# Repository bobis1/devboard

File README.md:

# Eduboard
A devboard with an inbuilt screen and a software platform that should help beginners learn the basics of computer science. This is a rp2040 devboard at it's core.

I made this project because I wanted some experience working with devboards before I start something more complex. I also wanted to make something where a microcontroller was on a devboard already.

### Pictures

Above are renders made in blender.

### Assembly
The assembly of the devboard is relatively straight forward. The first thing you need to do is you need to get a hotplate and some soder paste to carefully soder on all the SMD components onto the pcb(This will be new to me as I have never done it before). Then you need to soder on the header pins onto the pcb by placing your sodering iron on the joint between the pcb and the pin and putting solder into that joint.

### Flashing
The flashing of this works the same way as a normal raspberry pi pico. You need to hold down SW_1 to start the flashing process.

### BOM
This BOM is for non PCBA. To be clear, I plan on using the bill of materials labeled [BOM](BOM.csv), [BOM-PCBA](BOM-PCBA.csv) is a BOM if you want to PCBA part of it.

|Reference                          |Qty|Value                      |Footprint                                                 |Datasheet                                                                        |Description                                                                                                        |Shopping Link                                                                                                                                                                                                                                                                                                                                                                                                                                                                                                                                         |Unit Price|Prices|Notes                                      |
|-----------------------------------|---|---------------------------|----------------------------------------------------------|---------------------------------------------------------------------------------|-------------------------------------------------------------------------------------------------------------------|------------------------------------------------------------------------------------------------------------------------------------------------------------------------------------------------------------------------------------------------------------------------------------------------------------------------------------------------------------------------------------------------------------------------------------------------------------------------------------------------------------------------------------------------------|----------|------|-------------------------------------------|
|C1,C2,C3,C4,C5,C6,C7,C8,C10,C11,C17|11 |0.1uf                      |C_0402_1005Metric_Pad0.74x0.62mm_HandSolder               |                                                                                 |Unpolarized capacitor                                                                                              |https://www.lcsc.com/product-detail/C1591.html?s_z=s_p_CL10B104KB8NNNC                                                                                                                                                                                                                                                                                                                                                                                                                                                                                |$0.00     |$0.46 |Minimum quantity: 50                       |
|C9,C12                             |2  |1uf                        |C_0603_1608Metric_Pad1.08x0.95mm_HandSolder               |                                                                                 |Unpolarized capacitor                                                                                              |https://www.lcsc.com/product-detail/C59782.html?s_z=n_q_CL10B105KO8NNNC                                                                                                                                                                                                                                                                                                                                                                                                                                                                               |$0.02     |$1.06 |Minimum quantity: 50                       |
|C13,C14, C19                       |3  |10uf                       |Capacitor_SMD:C_0603_1608Metric_Pad1.08x0.95mm_HandSolder |                                                                                 |Unpolarized capacitor                                                                                              |Samsung Electro-Mechanics CL10A106KP8NNNC                                                                                                                                                                                                                                                                                                                                                                                                                                                                                                             |$0.01     |$0.54 |Minimum quantity: 50                       |
|C15,C16                            |2  |33uf                       |C_0402_1005Metric_Pad0.74x0.62mm_HandSolder               |                                                                                 |Unpolarized capacitor                                                                                              |https://www.lcsc.com/product-detail/C76930.html?s_z=n_q_p_Capacitor_SMD%253AC_0201_0603Metric_Pad0.64x0.40mm&spm=wm.ssy.bg.0.xh&lcsc_vid=E1MNX1EDFlVaVF0CR1dYUVRWE1hcUFBQRgNcBF1QRwUxVlNeT1NdVlNeQ1VZVDsOAxUeFF5JWBYZEEoKFBINSQcJGk4dAgUUFAk%3D                                                                                                                                                                                                                                                                                                       |$0.01     |$0.54 |Minimum quantity: 50                       |
|C18,C20,C21                        |3  |10μf                       |C_0402_1005Metric_Pad0.74x0.62mm_HandSolder               |                                                                                 |Unpolarized capacitor                                                                                              |Samsung Electro-Mechanics CL10A106KP8NNNC                                                                                                                                                                                                                                                                                                                                                                                                                                                                                                             |$0.01     |$0.54 |Minimum quantity: 50                       |
|J1                                 |1  |USB_C_Receptacle_USB2.0_14P|Connector_USB:USB_C_Receptacle_HRO_TYPE-C-31-M-12         |https://www.usb.org/sites/default/files/documents/usb_type-c.zip                 |USB 2.0-only 14P Type-C Receptacle connector                                                                       |https://www.lcsc.com/product-detail/C165948.html?spm=wm.fly.bg.0.xh&lcsc_vid=E1MNX1EDFlVaVF0CR1dYUVRWE1hcUFBQRgNcBF1QRwUxVlNeT1NdVlRQT1BdXjsOAxUeFF5JWBILBhYFH08MFQUQEk8NCAlJJ                                                                                                                                                                                                                                                                                                                                                                        |$0.17     |$0.86 |                                           |
|J2,J3                              |2  |Conn_01x20                 |Connector_PinHeader_1.00mm:PinHeader_1x20_P1.00mm_Vertical|                                                                                 |Generic connector, single row, 01x20, script generated (kicad-library-utils/schlib/autogen/connector/)             |https://www.aliexpress.us/item/3256811704196969.html?spm=a2g0o.order_list.order_list_main.5.52e91802DwzU5C&gatewayAdapt=glo2usa                                                                                                                                                                                                                                                                                                                                                                                                                       |$2.36     |$2.36 |Minimum quantity: 5                        |
|J4                                 |1  |Conn_01x03                 |Connector_PinHeader_1.00mm:PinHeader_1x03_P1.00mm_Vertical|                                                                                 |Generic connector, single row, 01x03, script generated (kicad-library-utils/schlib/autogen/connector/)             |https://www.aliexpress.us/item/3256811704196969.html?spm=a2g0o.order_list.order_list_main.5.52e91802DwzU5C&gatewayAdapt=glo2usa                                                                                                                                                                                                                                                                                                                                                                                                                       |$0.00     |$0.00 |                                           |
|L1                                 |1  |2.2μH                      |Inductor_SMD:L_6.3x6.3_H3                                 |                                                                                 |Inductor                                                                                                           |https://www.lcsc.com/product-detail/C52722262.html?s_z=h_q_inductor%25202.2uh&spm=wm.fly.bg.0.xh&lcsc_vid=E1MNX1EDFlVaVF0CR1dYUVRWE1hcUFBQRgNcBF1QRwUxVlNeT1NdV1xeRlFYVjsOAxUeFF5JWBYZEEoKFBINSQcJGk4eFQsCAgIaSgADAwAHC0slQ1lZX1dVR1NADxALGw%3D%3D                                                                                                                                                                                                                                                                                                    |$0.04     |$0.41 |This comes with the above 01x20 pin headers|
|R1                                 |1  |5.1KΩ                      |Resistor_SMD:R_0402_1005Metric_Pad0.72x0.64mm             |                                                                                 |Resistor                                                                                                           |https://www.mouser.com/en/ProductDetail/Vishay/CRCW04025K10FKED?qs=s0g2FHNyNFj8r6Uw5EJZ%2Fw%3D%3D                                                                                                                                                                                                                                                                                                                                                                                                                                                     |$0.10     |$0.10 |Minimum quanity: 10                        |
|R2                                 |1  |5.1KΩ                      |Resistor_SMD:R_0402_1005Metric_Pad0.72x0.64mm             |                                                                                 |Resistor                                                                                                           |https://www.mouser.com/en/ProductDetail/Vishay/CRCW04025K10FKED?qs=s0g2FHNyNFj8r6Uw5EJZ%2Fw%3D%3D                                                                                                                                                                                                                                                                                                                                                                                                                                                     |$0.10     |$0.10 |                                           |
|R3,R4                              |2  |27Ω                        |Resistor_SMD:R_0402_1005Metric_Pad0.72x0.64mm             |                                                                                 |Resistor                                                                                                           |https://www.mouser.com/en/ProductDetail/YAGEO/RC0402FR-0727RL?qs=UOUeRUa%252B8Wlb37UyFHw9Bw%3D%3D                                                                                                                                                                                                                                                                                                                                                                                                                                                     |$0.10     |$0.20 |                                           |
|R5,R6                              |2  |1KΩ                        |Resistor_SMD:R_0402_1005Metric_Pad0.72x0.64mm             |                                                                                 |Resistor                                                                                                           |https://www.mouser.com/en/ProductDetail/YAGEO/RC0402FR-071KL?qs=V1yeUXFNrknDEmWLmm5v6g%3D%3D                                                                                                                                                                                                                                                                                                                                                                                                                                                          |$0.10     |$0.20 |                                           |
|R7                                 |1  |10KΩ                       |Resistor_SMD:R_0402_1005Metric_Pad0.72x0.64mm             |                                                                                 |Resistor                                                                                                           |https://www.mouser.com/en/ProductDetail/YAGEO/RC0402FR-0710KL?qs=I1mnnYJTTsxUoNwrUsQExA%3D%3D                                                                                                                                                                                                                                                                                                                                                                                                                                                         |$0.10     |$0.10 |                                           |
|R8                                 |1  |100Ω                       |Resistor_SMD:R_0402_1005Metric_Pad0.72x0.64mm             |                                                                                 |Resistor                                                                                                           |https://www.mouser.com/en/ProductDetail/Vishay/CRCW0402100RFKED?qs=OlqPY1CiralT1EG%2F62gJpQ%3D%3D                                                                                                                                                                                                                                                                                                                                                                                                                                                     |$0.10     |$0.10 |                                           |
|SW1,SW2                            |2  |SW_Push                    |Button_Switch_SMD:SW_SPST_TS-1088-xR020                   |                                                                                 |Push button switch, generic, two pins                                                                              |https://www.lcsc.com/product-detail/C49234124.html?s_z=n_q_t_tactile%2520switches%2520smd&spm=wm.fly.bg.1.xh___wm.ssy.tc.0.tz&lcsc_vid=E1MNX1EDFlVaVF0CR1dYUVRWE1hcUFBQRgNcBF1QRwUxVlNeT1BdV1RQQlVaXzsOAxUeFF5JWBYZEEoKFBINSQcJGk4dAgUUFAk%3D                                                                                                                                                                                                                                                                                                         |$0.02     |$0.49 |                                           |
|U1                                 |1  |RP2040                     |Package_DFN_QFN:QFN-56-1EP_7x7mm_P0.4mm_EP3.2x3.2mm       |https://datasheets.raspberrypi.com/rp2040/rp2040-datasheet.pdf                   |A microcontroller by Raspberry Pi, Dual ARM Cortex-M0+, 133MHz, no flash, 264KB SRAM, 8 PIO state machines, VQFN-56|https://www.digikey.com/en/products/detail/raspberry-pi/SC0908-7/14306009?src=raspberrypi                                                                                                                                                                                                                                                                                                                                                                                                                                                             |$0.92     |$0.92 |                                           |
|U2                                 |1  |MCP1700x-120xxMB           |Package_TO_SOT_SMD:SOT-89-3                               |http://ww1.microchip.com/downloads/en/DeviceDoc/20001826D.pdf                    |250mA Low Quiscent Current LDO, 1.2V output, SOT-89                                                                |https://www.microchip.com/en-us/product/mcp1700#Purchase(3 leads, SOT-89 packaging)                                                                                                                                                                                                                                                                                                                                                                                                                                                                   |$0.51     |$0.51 |                                           |
|U3                                 |1  |W25Q128JVS                 |Package_SO:SOIC-8_5.3x5.3mm_P1.27mm                       |https://www.winbond.com/resource-files/w25q128jv_dtr%20revc%2003272018%20plus.pdf|128Mbit / 16MiB Serial Flash Memory, Standard/Dual/Quad SPI, 2.7-3.6V, SOIC-8                                      |https://www.lcsc.com/product-detail/C97521.html?s_z=n_q_p_128M-BIT%2520SERIAL%2520FLASH%2520MEMORY%2520WITH%2520DUAL%252FQUAD%2520SPI&spm=wm.ssy.bg.23.xh&lcsc_vid=E1MNX1EDFlVaVF0CR1dYUVRWE1hcUFBQRgNcBF1QRwUxVlNeT1BcXlFfTlBWVTsOAxUeFF5JWBYZEEoKFBINSQcJGk4dAgUUFAk%3D OR https://www.lcsc.com/product-detail/C97521.html?s_z=n_q_p_128M-BIT%2520SERIAL%2520FLASH%2520MEMORY%2520WITH%2520DUAL%252FQUAD%2520SPI&spm=wm.ssy.bg.22.xh&lcsc_vid=E1MNX1EDFlVaVF0CR1dYUVRWE1hcUFBQRgNcBF1QRwUxVlNeT1BcXlFfTlBWVTsOAxUeFF5JWBYZEEoKFBINSQcJGk4dAgUUFAk%3D|$2.62     |$2.62 |                                           |
|U4                                 |1  |ER_OLEDM0.91_1x-I2C        |Display:ER_OLEDM0.91_1x-I2C                               |https://www.buydisplay.com/download/manual/ER-OLEDM0.91-1_Datasheet.pdf          |SSD1306 OLED module, 0.91 inch, 128x32, I2C                                                                        |https://www.buydisplay.com/i2c-white-0-91-inch-oled-display-module-128x32-arduino-raspberry-pi                                                                                                                                                                                                                                                                                                                                                                                                                                                        |$2.80     |$2.80 |                                           |
|U5                                 |1  |TPS63000                   |Package_SON:Texas_DRC0010J_ThermalVias                    |http://www.ti.com/lit/ds/symlink/tps63000.pdf                                    |Buck-Boost Converter, 1.8-5.5V Input Voltage, 1.8A Switch Current, Adjustable 1.2-5.5V Output Voltage, VSON-10     |https://www.ti.com/product/TPS63000/part-details/TPS63000DRCR                                                                                                                                                                                                                                                                                                                                                                                                                                                                                         |$2.00     |$2.00 |                                           |
|XT1                                |1  |                           |JST-PH-2.:JST-PH-2                                        |                                                                                 |                                                                                                                   |https://www.adafruit.com/product/1769                                                                                                                                                                                                                                                                                                                                                                                                                                                                                                                 |$0.75     |$0.75 |                                           |
|Y2                                 |1  |Crystal_GND24              |Crystal:Crystal_SMD_3225-4Pin_3.2x2.5mm                   |                                                                                 |Four pin crystal, GND on pins 2 and 4                                                                              |https://www.lcsc.com/product-detail/C13738.html?s_z=n_q_p_crystal%25203225-4Pin_3.2x2.5mm&spm=wm.ssy.bg.0.xh&lcsc_vid=E1MNX1EDFlVaVF0CR1dYUVRWE1hcUFBQRgNcBF1QRwUxVlNeT1BcX1JRQFhYUDsOAxUeFF5JWBYZEEoKFBINSQcJGk4%3D                                                                                                                                                                                                                                                                                                                                  |$0.09     |$0.47 |                                           |
|                                   |   |                           |                                                          |                                                                                 |                                                                                                                   |                                                                                                                                                                                                                                                                                                                                                                                                                                                                                                                                                      |          |      |Minimum quanity: 5                         |
|                                   |   |                           |                                                          |                                                                                 |                                                                                                                   |                                                                                                                                                                                                                                                                                                                                                                                                                                                                                                                                                      |          |      |                                           |
|                                   |   |                           |                                                          |                                                                                 |                                                                                                                   |                                                                                                                                                                                                                                                                                                                                                                                                                                                                                                                                                      |          |      |                                           |
|                                   |   |                           |Subtotal:                                                 |$0.00                                                                            |                                                                                                                   |                                                                                                                                                                                                                                                                                                                                                                                                                                                                                                                                                      |          |      |                                           |
|                                   |   |                           |PCB Fee:                                                  |$0.00                                                                            |                                                                                                                   |                                                                                                                                                                                                                                                                                                                                                                                                                                                                                                                                                      |          |      |                                           |
|                                   |   |                           |Shipping:                                                 |$2.00                                                                            |                                                                                                                   |                                                                                                                                                                                                                                                                                                                                                                                                                                                                                                                                                      |          |      |                                           |
|                                   |   |                           |Tariff:                                                   |$0.00                                                                            |                                                                                                                   |                                                                                                                                                                                                                                                                                                                                                                                                                                                                                                                                                      |          |      |                                           |
|                                   |   |                           |PCBA fee:                                                 |$45.96                                                                           |                                                                                                                   |                                                                                                                                                                                                                                                                                                                                                                                                                                                                                                                                                      |          |      |                                           |
|                                   |   |                           |Total Price                                               |$47.96                                                                           |                                                                                                                   |                                                                                                                                                                                                                                                                                                                                                                                                                                                                                                                                                      |          |      |                                           |

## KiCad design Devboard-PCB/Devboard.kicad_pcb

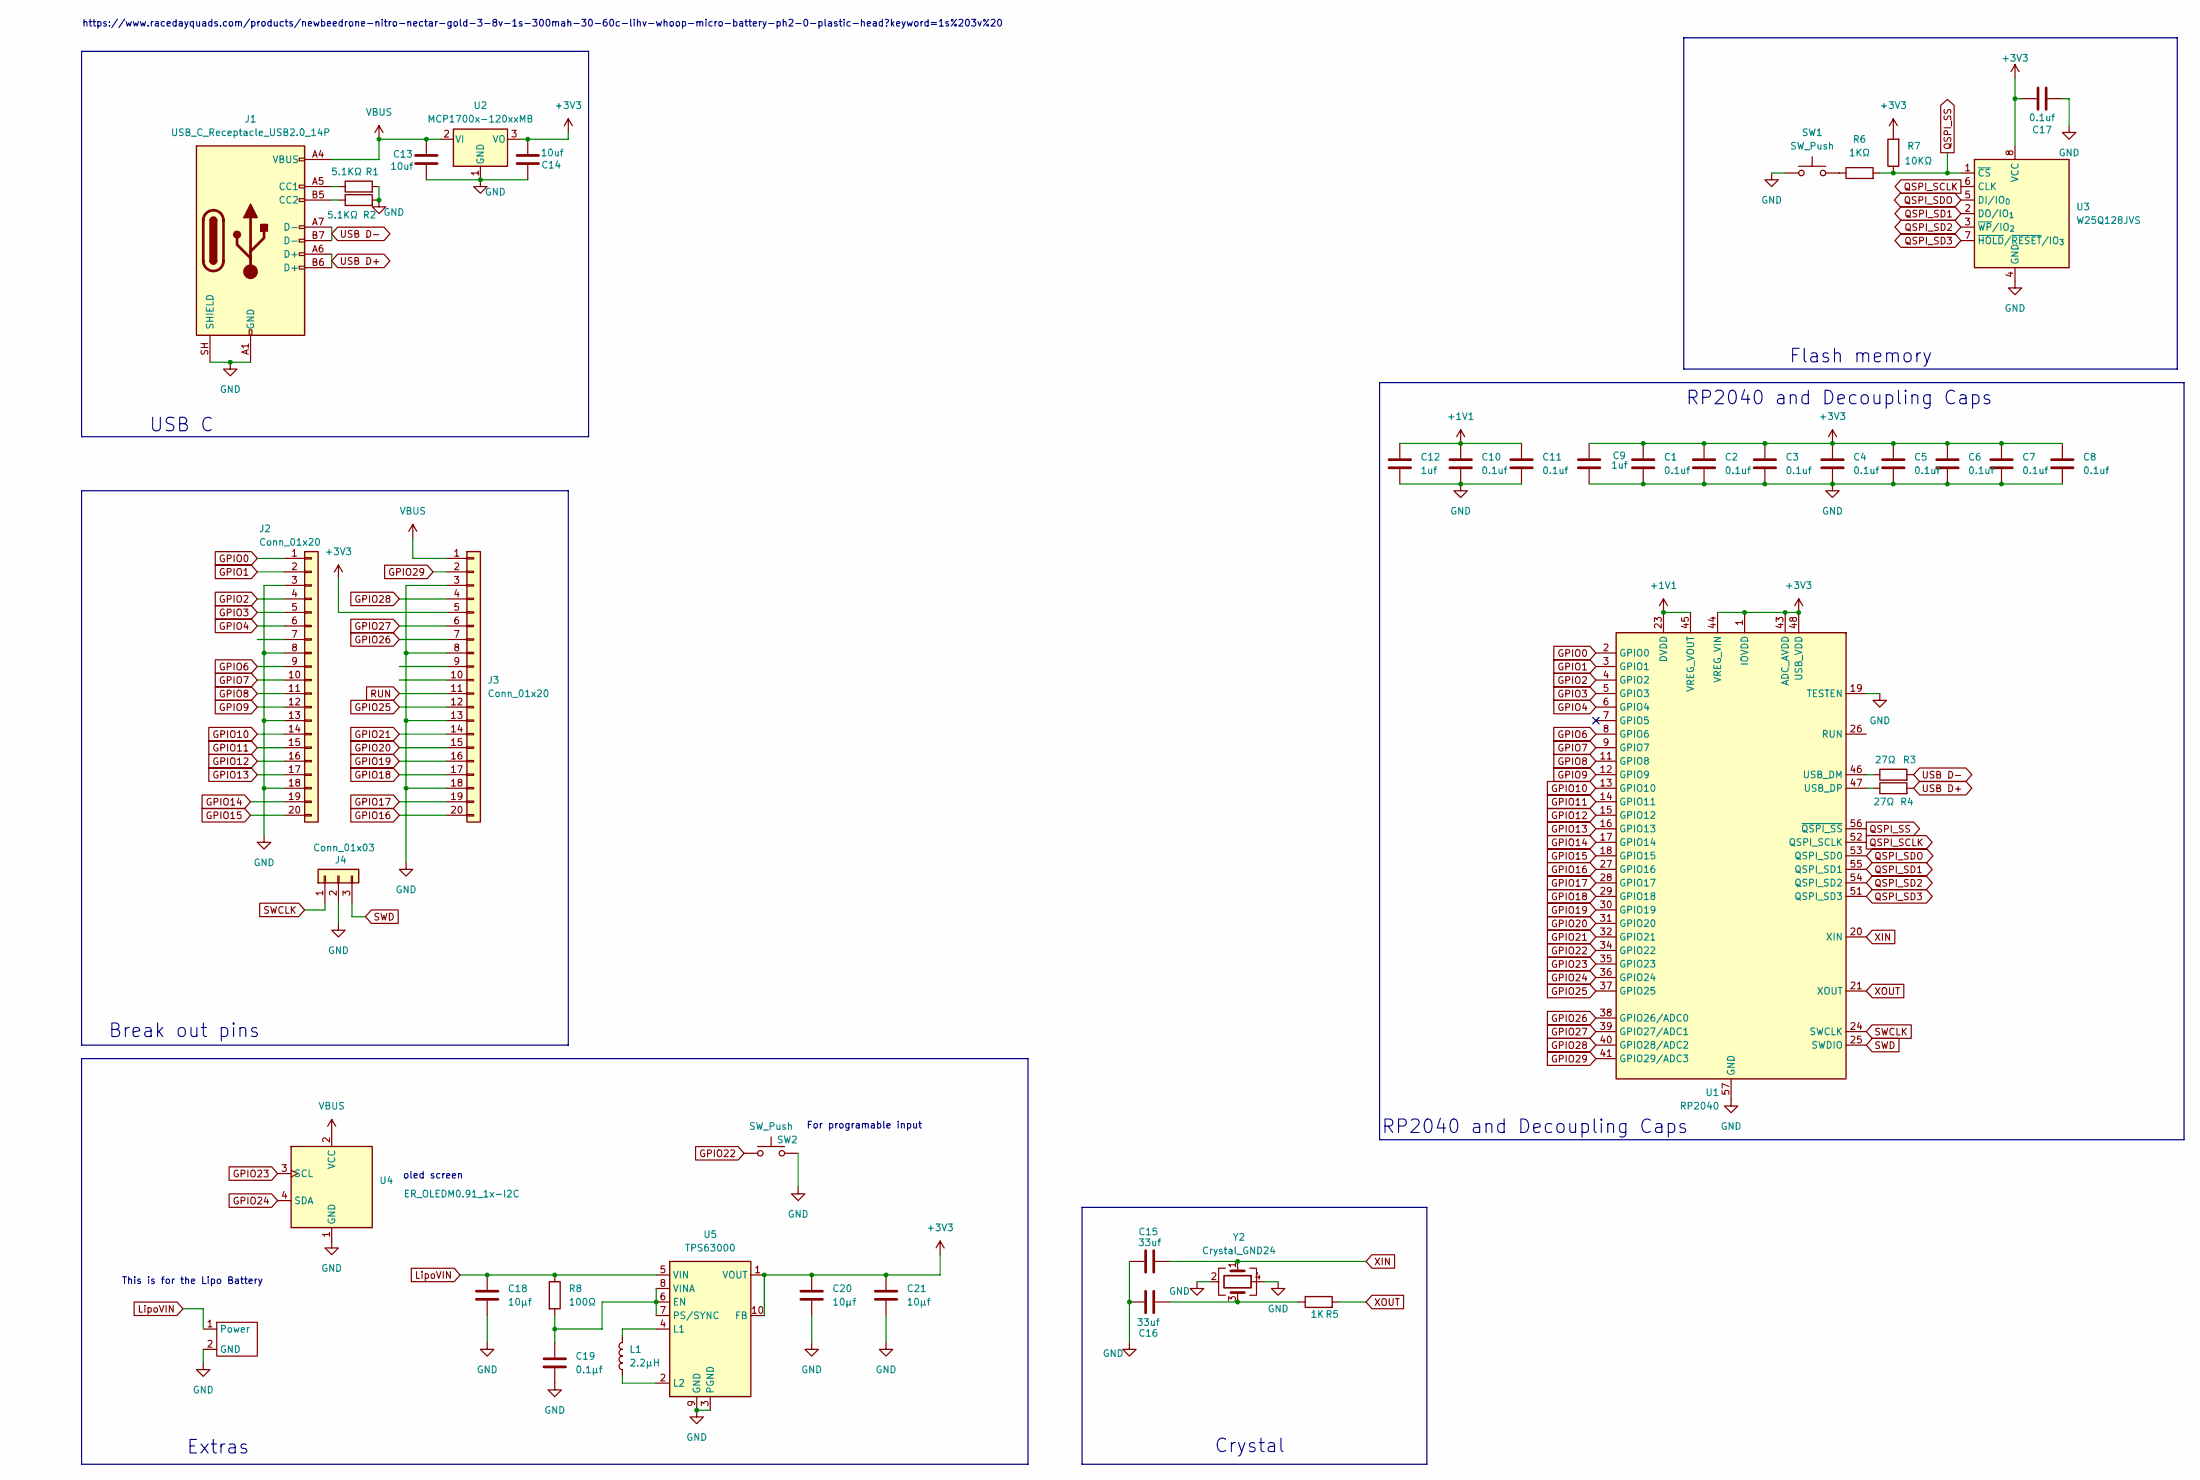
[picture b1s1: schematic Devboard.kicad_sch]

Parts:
C1, C2, C3, C4, C5, C6, C7, C8, C10, C11, C17: 0.1uf; C_0402_1005Metric_Pad0.74x0.62mm_HandSolder
C9: 1uf; C_0603_1608Metric_Pad1.08x0.95mm_HandSolder
C12: 1uf; C_0402_1005Metric_Pad0.74x0.62mm_HandSolder
C13, C14: 10uf; C_0402_1005Metric_Pad0.74x0.62mm_HandSolder
C15, C16: 33uf; C_0402_1005Metric_Pad0.74x0.62mm_HandSolder
C18, C20, C21: 10μf; C_0603_1608Metric_Pad1.08x0.95mm_HandSolder
C19: 0.1μf; C_0402_1005Metric_Pad0.74x0.62mm_HandSolder
J1: USB_C_Receptacle_USB2.0_14P; USB_C_Receptacle_HRO_TYPE-C-31-M-12
J2, J3: Conn_01x20; PinHeader_1x20_P1.00mm_Vertical
J4: Conn_01x03; PinHeader_1x03_P1.00mm_Vertical
L1: 2.2μH; L_6.3x6.3_H3
R1, R2: 5.1KΩ; R_0402_1005Metric
R3, R4: 27Ω; R_0402_1005Metric
R5: 1K; R_0402_1005Metric
R6: 1KΩ; R_0402_1005Metric
R7: 10KΩ; R_0402_1005Metric
R8: 100Ω; R_0201_0603Metric
SW1, SW2: SW_Push; SW_SPST_TS-1088-xR020
U1: RP2040; QFN-56-1EP_7x7mm_P0.4mm_EP3.2x3.2mm
U2: MCP1700x-120xxMB; SOT-89-3
U3: W25Q128JVS; SOIC-8_5.3x5.3mm_P1.27mm
U4: ER_OLEDM0.91_1x-I2C
U5: TPS63000; Texas_DRC0010J_ThermalVias
XT1: JST-PH-2
Y2: Crystal_GND24; Crystal_SMD_3225-4Pin_3.2x2.5mm

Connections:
+1V1: C10.1, C11.1, C12.1, U1.23 (DVDD), U1.45 (VREG_VOUT), U1.50 (DVDD)
+3V3: C1.1, C2.1, C3.1, C4.1, C5.1, C6.1, C7.1, C8.1, C9.1, C14.2, C17.1, C20.1, C21.1, J3.5, R7.2, U1.1 (IOVDD), U1.10 (IOVDD), U1.22 (IOVDD), U1.33 (IOVDD), U1.42 (IOVDD), U1.43 (ADC_AVDD), U1.44 (VREG_VIN), U1.48 (USB_VDD), U1.49 (IOVDD), U2.3 (VO), U3.8 (VCC), U5.1 (VOUT), U5.10 (FB)
GND: C1.2, C2.2, C3.2, C4.2, C5.2, C6.2, C7.2, C8.2, C9.2, C10.2, C11.2, C12.2, C13.2, C14.1, C15.1, C16.1, C17.2, C18.2, C19.2, C20.2, C21.2, J1.A1 (GND), J1.A12 (GND), J1.B1 (GND), J1.B12 (GND), J1.SH (SHIELD), J2.3, J2.8, J2.13, J2.18, J3.3, J3.8, J3.13, J3.18, J4.2, R1.2, R2.2, SW1.1, SW2.2, U1.19 (TESTEN), U1.57 (GND), U2.1 (GND), U3.4 (GND), U4.1 (GND), U5.3 (PGND), U5.9 (GND), U5.11 (PGND), XT1.2 (GND), Y2.2 (G), Y2.4 (G)
GPIO0: J2.1, U1.2 (GPIO0)
GPIO1: J2.2, U1.3 (GPIO1)
GPIO2: J2.4, U1.4 (GPIO2)
GPIO3: J2.5, U1.5 (GPIO3)
GPIO4: J2.6, U1.6 (GPIO4)
GPIO6: J2.9, U1.8 (GPIO6)
GPIO7: J2.10, U1.9 (GPIO7)
GPIO8: J2.11, U1.11 (GPIO8)
GPIO9: J2.12, U1.12 (GPIO9)
GPIO10: J2.14, U1.13 (GPIO10)
GPIO11: J2.15, U1.14 (GPIO11)
GPIO12: J2.16, U1.15 (GPIO12)
GPIO13: J2.17, U1.16 (GPIO13)
GPIO14: J2.19, U1.17 (GPIO14)
GPIO15: J2.20, U1.18 (GPIO15)
GPIO16: J3.20, U1.27 (GPIO16)
GPIO17: J3.19, U1.28 (GPIO17)
GPIO18: J3.17, U1.29 (GPIO18)
GPIO19: J3.16, U1.30 (GPIO19)
GPIO20: J3.15, U1.31 (GPIO20)
GPIO21: J3.14, U1.32 (GPIO21)
GPIO22: SW2.1, U1.34 (GPIO22)
GPIO23: U1.35 (GPIO23), U4.3 (SCL)
GPIO24: U1.36 (GPIO24), U4.4 (SDA)
GPIO25: J3.12, U1.37 (GPIO25)
GPIO26: J3.7, U1.38 (GPIO26/ADC0)
GPIO27: J3.6, U1.39 (GPIO27/ADC1)
GPIO28: J3.4, U1.40 (GPIO28/ADC2)
GPIO29: J3.2, U1.41 (GPIO29/ADC3)
LipoVIN: C18.1, R8.1, U5.5 (VIN), XT1.1 (Power)
unnamed: C16.2, R5.1, Y2.3
unnamed: J1.A5 (CC1), R1.1
unnamed: J1.B5 (CC2), R2.1
unnamed: R6.1, SW1.2
unnamed: R3.1, U1.46 (USB_DM)
unnamed: R4.1, U1.47 (USB_DP)
unnamed: C19.1, R8.2, U5.6 (EN), U5.7 (PS/SYNC), U5.8 (VINA)
unnamed: L1.2, U5.4 (L1)
unnamed: L1.1, U5.2 (L2)
QSPI_SCLK: U1.52 (QSPI_SCLK), U3.6 (CLK)
QSPI_SD1: U1.55 (QSPI_SD1), U3.2 (DO/IO_{1})
QSPI_SD2: U1.54 (QSPI_SD2), U3.3 (~WP/IO_{2})
QSPI_SD3: U1.51 (QSPI_SD3), U3.7 (~HOLD/~RESET/IO_{3})
QSPI_SDO: U1.53 (QSPI_SD0), U3.5 (DI/IO_{0})
QSPI_SS: R6.2, R7.1, U1.56 (~QSPI_SS), U3.1 (~CS)
RUN: J3.11
SWCLK: J4.1, U1.24 (SWCLK)
SWD: J4.3, U1.25 (SWDIO)
USB D+: J1.A6 (D+), J1.B6 (D+), R4.2
USB D-: J1.A7 (D-), J1.B7 (D-), R3.2
VBUS: C13.1, J1.A4 (VBUS), J1.A9 (VBUS), J1.B4 (VBUS), J1.B9 (VBUS), J3.1, U2.2 (VI), U4.2 (VCC)
XIN: C15.2, U1.20 (XIN), Y2.1
XOUT: R5.2, U1.21 (XOUT)

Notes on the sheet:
Break out pins
https://www.racedayquads.com/products/newbeedrone-nitro-nectar-gold-3-8v-1s-300mah-30-60c-lihv-whoop-micro-battery-ph2-0-plastic-head?keyword=1s%203v%20
Flash memory
USB C
RP2040 and Decoupling Caps
Extras
Crystal
oled screen
This is for the Lipo Battery
For programable input

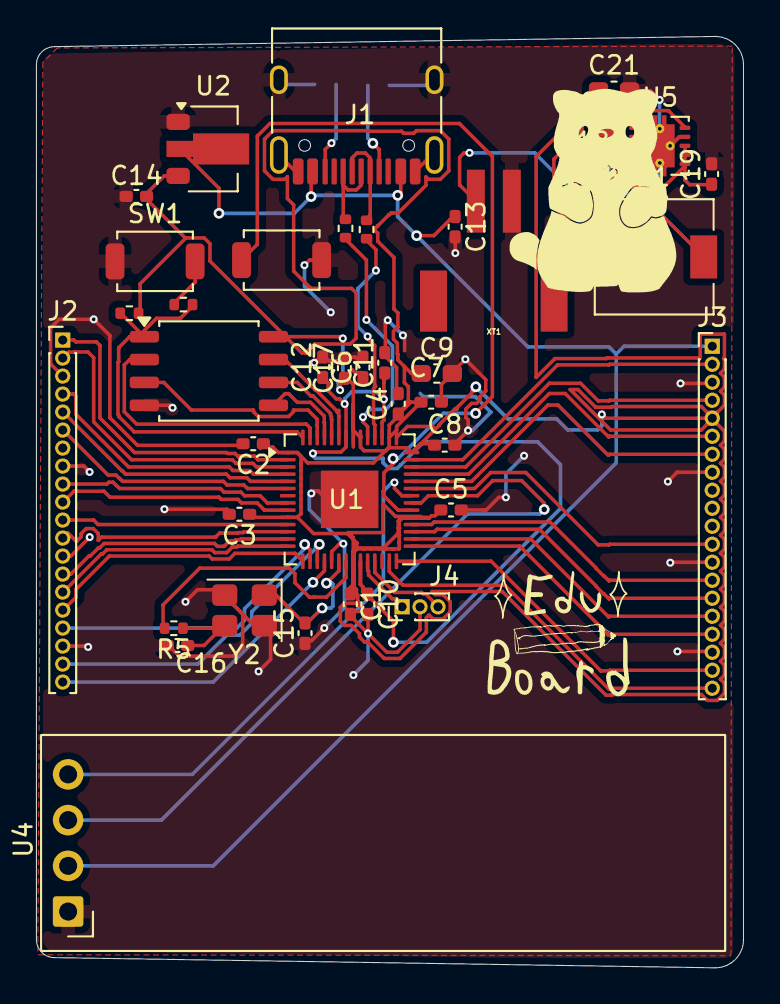
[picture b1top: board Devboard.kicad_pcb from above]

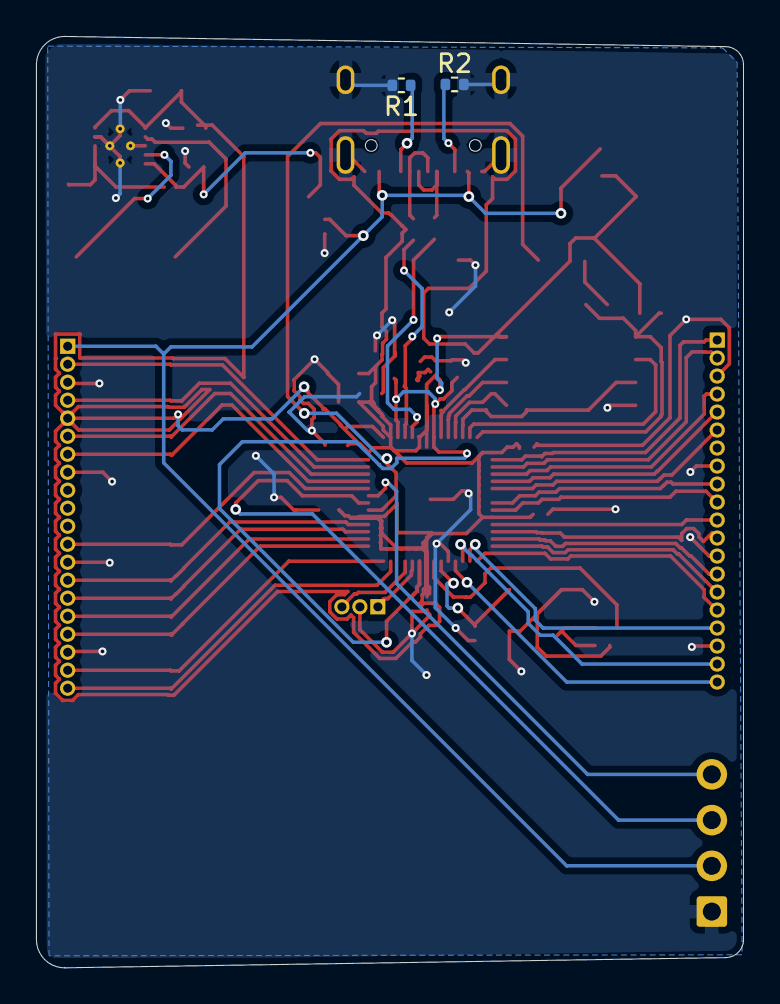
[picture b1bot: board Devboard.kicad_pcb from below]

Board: 2 copper layers, 39.3 x 51.7 mm, 43 parts (2 on the bottom side), 55 nets.

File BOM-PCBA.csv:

Reference,Qty,Value,Footprint,Datasheet,Description,Shopping Link,Unit Price,Prices,Notes
"C1,C2,C3,C4,C5,C6,C7,C8,C10,C11,C17",11,0.1uf,Capacitor_SMD:C_0201_0603Metric_Pad0.64x0.40mm,,Unpolarized capacitor,https://www.lcsc.com/product-detail/C76930.html?s_z=n_q_p_Ca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,$0.01,$0.54,Minimum quantity: 50
"C9,C12",2,1uf,Capacitor_SMD:C_0201_0603Metric_Pad0.64x0.40mm,,Unpolarized capacitor,https://www.lcsc.com/product-detail/C76930.html?s_z=n_q_p_Ca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,$0.01,$0.54,Minimum quantity: 50
"C13,C14",2,10uf,Capacitor_SMD:C_0201_0603Metric_Pad0.64x0.40mm,,Unpolarized capacitor,https://www.lcsc.com/product-detail/C76930.html?s_z=n_q_p_Ca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,$0.01,$0.54,Minimum quantity: 50
"C15,C16",2,33uf,Capacitor_SMD:C_0201_0603Metric_Pad0.64x0.40mm,,Unpolarized capacitor,https://www.lcsc.com/product-detail/C76930.html?s_z=n_q_p_Ca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,$0.01,$0.54,Minimum quantity: 50
"C18,C20,C21",3,10μf,Capacitor_SMD:C_0201_0603Metric_Pad0.64x0.40mm,,Unpolarized capacitor,https://www.lcsc.com/product-detail/C76930.html?s_z=n_q_p_Ca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,$0.01,$0.54,Minimum quantity: 50
C19,1,0.1μf,Capacitor_SMD:C_0201_0603Metric_Pad0.64x0.40mm,,Unpolarized capacitor,https://www.lcsc.com/product-detail/C76930.html?s_z=n_q_p_Ca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,$0.01,$0.54,Minimum quantity: 50
J1,1,USB_C_Receptacle_USB2.0_14P,Connector_USB:USB_C_Receptacle_HRO_TYPE-C-31-M-12,https://www.usb.org/sites/default/files/documents/usb_type-c.zip,USB 2.0-only 14P Type-C Receptacle connector,https://www.lcsc.com/product-detail/C165948.html?spm=wm.fly.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,$0.17,$0.86,Minimum quantity: 5
"J2,J3",2,Conn_01x20,Connector_PinHeader_1.00mm:PinHeader_1x20_P1.00mm_Vertical,,"Generic connector, single row, 01x20, script generated (kicad-library-utils/schlib/autogen/connector/)",https://www.aliexpress.us/item/3256811704196969.html?spm=a2g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,$2.36,$2.36,
J4,1,Conn_01x03,Connector_PinHeader_1.00mm:PinHeader_1x03_P1.00mm_Vertical,,"Generic connector, single row, 01x03, script generated (kicad-library-utils/schlib/autogen/connector/)",https://www.aliexpress.us/item/3256811704196969.html?spm=a2g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,$0.00,$0.00,This comes with the above 01x20 pin headers
L1,1,2.2μH,Inductor_SMD:L_6.3x6.3_H3,,Inductor,https://www.lcsc.com/product-detail/C52722262.html?s_z=h_q_i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,$0.04,$0.41,Minimum quanity: 10
R1,1,5.1KΩ,Resistor_SMD:R_0402_1005Metric_Pad0.72x0.64mm,,Resistor,https://www.mouser.com/en/ProductDetail/Vishay/CRCW04025K10F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,$0.10,$0.10,
R2,1,5.1KΩ,Resistor_SMD:R_0402_1005Metric_Pad0.72x0.64mm,,Resistor,https://www.mouser.com/en/ProductDetail/Vishay/CRCW04025K10F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,$0.10,$0.10,
"R3,R4",2,27Ω,Resistor_SMD:R_0402_1005Metric_Pad0.72x0.64mm,,Resistor,https://www.mouser.com/en/ProductDetail/YAGEO/RC0402FR-0727R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,$0.10,$0.20,
"R5,R6",2,1KΩ,Resistor_SMD:R_0402_1005Metric_Pad0.72x0.64mm,,Resistor,https://www.mouser.com/en/ProductDetail/YAGEO/RC0402FR-071KL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,$0.10,$0.20,
R7,1,10KΩ,Resistor_SMD:R_0402_1005Metric_Pad0.72x0.64mm,,Resistor,https://www.mouser.com/en/ProductDetail/YAGEO/RC0402FR-0710K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,$0.10,$0.10,
R8,1,100Ω,Resistor_SMD:R_0402_1005Metric_Pad0.72x0.64mm,,Resistor,https://www.mouser.com/en/ProductDetail/Vishay/CRCW0402100RF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,$0.10,$0.10,
"SW1,SW2",2,SW_Push,Button_Switch_SMD:SW_SPST_TS-1088-xR020,,"Push button switch, generic, two pins",https://www.lcsc.com/product-detail/C49234124.html?s_z=n_q_t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,$0.02,$0.49,
U1,1,RP2040,Package_DFN_QFN:QFN-56-1EP_7x7mm_P0.4mm_EP3.2x3.2mm,https://datasheets.raspberrypi.com/rp2040/rp2040-datasheet.pdf,"A microcontroller by Raspberry Pi, Dual ARM Cortex-M0+, 133MHz, no flash, 264KB SRAM, 8 PIO state machines, VQFN-56",https://www.digikey.com/en/products/detail/raspberry-pi/SC09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,$0.92,$0.92,
U2,1,MCP1700x-120xxMB,Package_TO_SOT_SMD:SOT-89-3,http://ww1.microchip.com/downloads/en/DeviceDoc/20001826D.pdf,"250mA Low Quiscent Current LDO, 1.2V output, SOT-89","https://www.microchip.com/en-us/product/mcp1700#Purchase(3 leads, SOT-89 packaging)",$0.51,$0.51,
U3,1,W25Q128JVS,Package_SO:SOIC-8_5.3x5.3mm_P1.27mm,https://www.winbond.com/resource-files/w25q128jv_dtr%20revc%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,"128Mbit / 16MiB Serial Flash Memory, Standard/Dual/Quad SPI, 2.7-3.6V, SOIC-8",https://www.lcsc.com/product-detail/C97521.html?s_z=n_q_p_12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 OR https://www.lcsc.com/product-detail/C97521.html?s_z=n_q_p_12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,$2.62,$2.62,
U4,1,ER_OLEDM0.91_1x-I2C,Display:ER_OLEDM0.91_1x-I2C,https://www.buydisplay.com/download/manual/ER-OLEDM0.91-1_Da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,"SSD1306 OLED module, 0.91 inch, 128x32, I2C",https://www.buydisplay.com/i2c-white-0-91-inch-oled-display-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,$2.80,$2.80,
U5,1,TPS63000,Package_SON:Texas_DRC0010J_ThermalVias,http://www.ti.com/lit/ds/symlink/tps63000.pdf,"Buck-Boost Converter, 1.8-5.5V Input Voltage, 1.8A Switch Current, Adjustable 1.2-5.5V Output Voltage, VSON-10",https://www.ti.com/product/TPS63000/part-details/TPS63000DRCR,$2.00,$2.00,
XT1,1,,JST-PH-2.:JST-PH-2,,,https://www.adafruit.com/product/1769,$0.75,$0.75,
Y2,1,Crystal_GND24,Crystal:Crystal_SMD_3225-4Pin_3.2x2.5mm,,"Four pin crystal, GND on pins 2 and 4",https://www.lcsc.com/product-detail/C13738.html?s_z=n_q_p_cr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,$0.09,$0.47,Minimum quanity: 5
,,,,,,,,,
,,,,,,,,,
,,,Subtotal:,$0.00,,,,,
,,,PCB Fee:,$0.00,,,,,
,,,Shipping:,$2.00,,,,,
,,,Tariff:,$0.00,,,,,
,,,PCBA fee:,$45.96,,,,,
,,,Total Price,$47.96,,,,,

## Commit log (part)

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2026-05-03 Worked on schematic
2026-05-04 Worked on adding batteries and an oled screen.
2026-05-05 Worked on routing
2026-05-06 Routed the pins more.
2026-05-07 Worked on routing the PCB more
2026-05-11 Worked on more routing
2026-05-12 Routing part 2 electric boogalooo
2026-05-15 Lowk forgot to push yesterday but did more routing
    yesterday I made ok progress. I need to move the pins tho
2026-05-18 Finished routing
    A pretty productive day so far
2026-05-21 Worked on the art of devboard
    Got the assets made and started to implement them.
2026-05-22 Worked on the firmware and the godot app
    ok progress
2026-05-28 Worked on getting the basic constructor ui set up
    goodish progress
2026-05-30 Updated Journal
